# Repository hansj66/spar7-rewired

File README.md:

# Spar7 Rewired

This repository contains schematics, PCB layout, gerber files and STEP/STL files necessary for a complete Spar 7 rebuild.

 > **Disclaimer:** This repository contains information about my own rebuild. I can not guarantee that this will work as expected in YOUR game. It is entirely possible that you will break your beautiful collector quality game beyond repair trying to retrofit this board and the 3D printed hopper mechanism. Proceed at your own risk :)

Note: The payout slide is currently made of 1.7mm thick 3D printed plastic. This part will wear out over time, and the life expectancy of this part is currently unknown. A CNC fabricated aluminium/steel sheet with 3D printed endcaps is a better option if this is a concern.

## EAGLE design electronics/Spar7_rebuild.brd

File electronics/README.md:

# Eagle files

Here you will find a bill of materials along with eagle project files. Gerber files that can be uploaded to a PCB manufacturer can be found in the CAM folder

## Notes
1. There is no hardware debouncing in this version. A RC filter + schmitt trigger should be added to the inputs if you are planing on using interrupt handlers for the inputs.
2. The relay is rated for higher voltages than 12V, but I would not recommend using this for controlling a line voltage driven AC motor (220V can kill).
3. The 3.3V, 12V and USB leds are a bit on the bright side. Use series resistors with a higher resistance or consider not mounting these LEDs if light leakage to the payout slot is considered annoying.

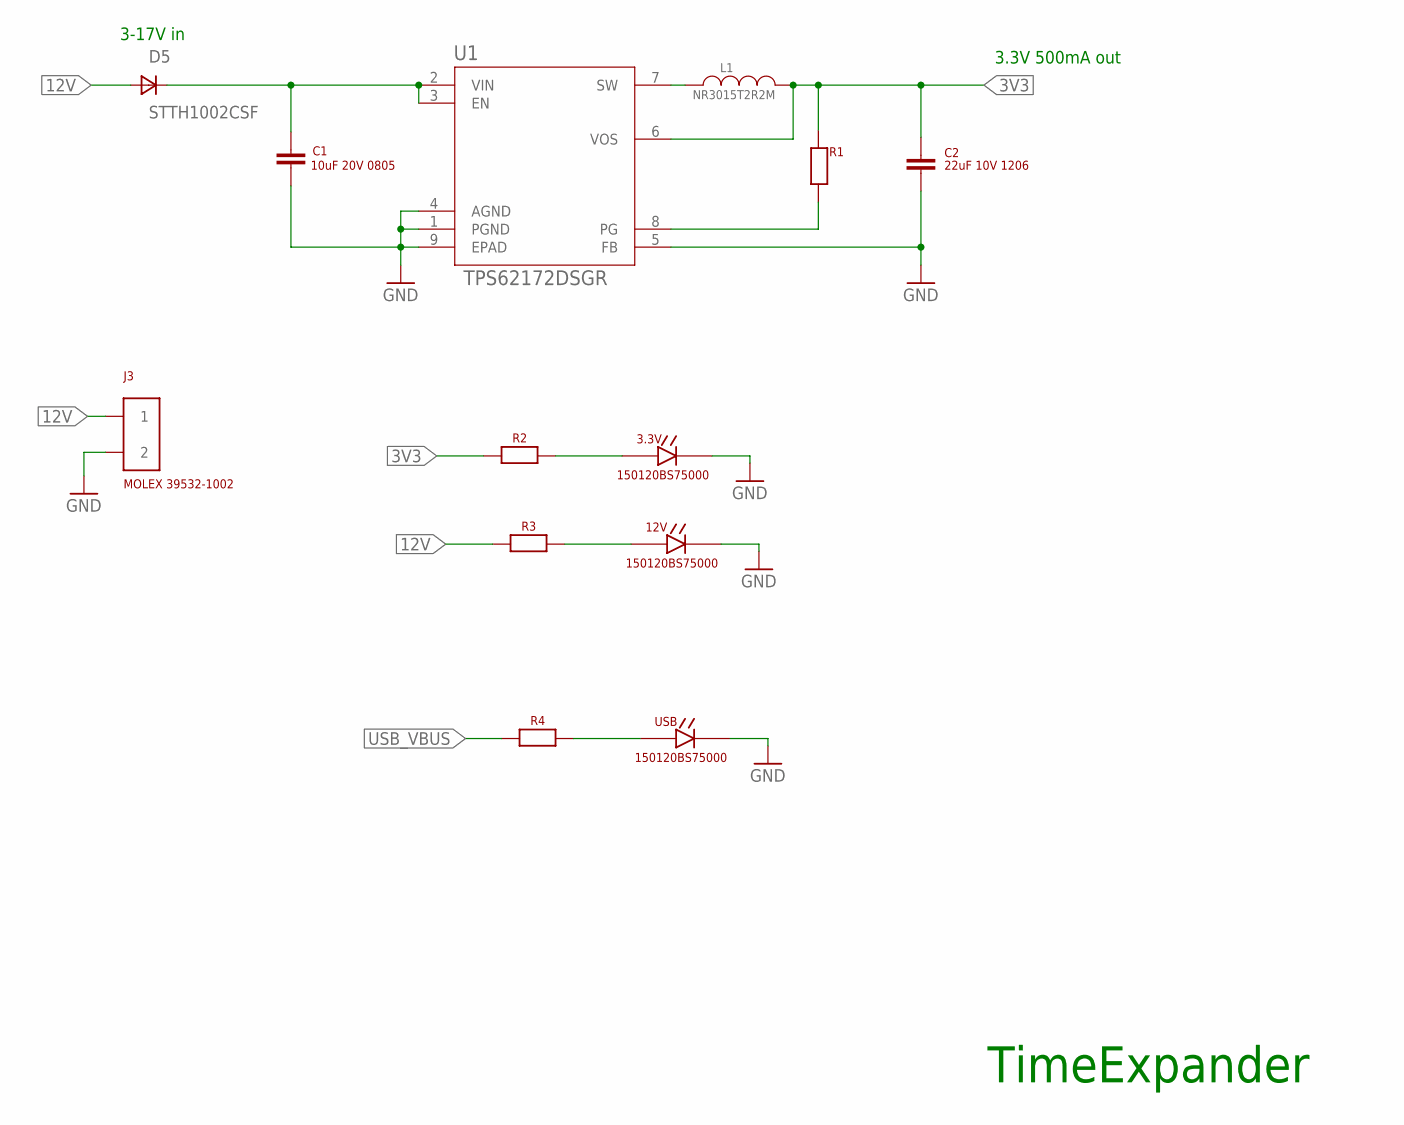
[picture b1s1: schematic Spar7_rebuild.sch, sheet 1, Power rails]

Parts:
3.3V, 12V: 150120BS75000
C1: 10uF 20V 0805; CAP_0805
C2: 22uF 10V 1206; CAP_1206
D5: STTH1002CSF; DIODE_STTH1002CSF
J3: MOLEX-39532-1002
L1: NR3015T2R2M; IND_TAIYO_NR3015_TAY
R1, R2, R3, R4: RESISTOR0402; RES_0402
U1: TPS62172DSGR; DSG8_1P6X0P9
USB: 150120BS75000

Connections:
3V3: C2.P$1 (1), L1.1, R1.P$1, R2.P$1, U1.6 (VOS); also elsewhere on the board
12V: D5.A1 (A), D5.A2 (A), J3.1, R3.P$1; also elsewhere on the board
GND: 3.3V.C, 12V.C, C1.P$2 (2), C2.P$2 (2), J3.2, U1.1 (PGND), U1.4 (AGND), U1.5 (FB), U1.9 (EPAD), USB.C; also elsewhere on the board
unnamed: L1.2, U1.7 (SW)
unnamed: 12V.A, R3.P$2
unnamed: R1.P$2, U1.8 (PG)
unnamed: R4.P$2, USB.A
unnamed: 3.3V.A, R2.P$2
unnamed: C1.P$1 (1), D5.C, U1.2 (VIN), U1.3 (EN)
USB_VBUS: R4.P$1; also elsewhere on the board

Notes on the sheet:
3.3V 500mA out
3-17V in
TimeExpander

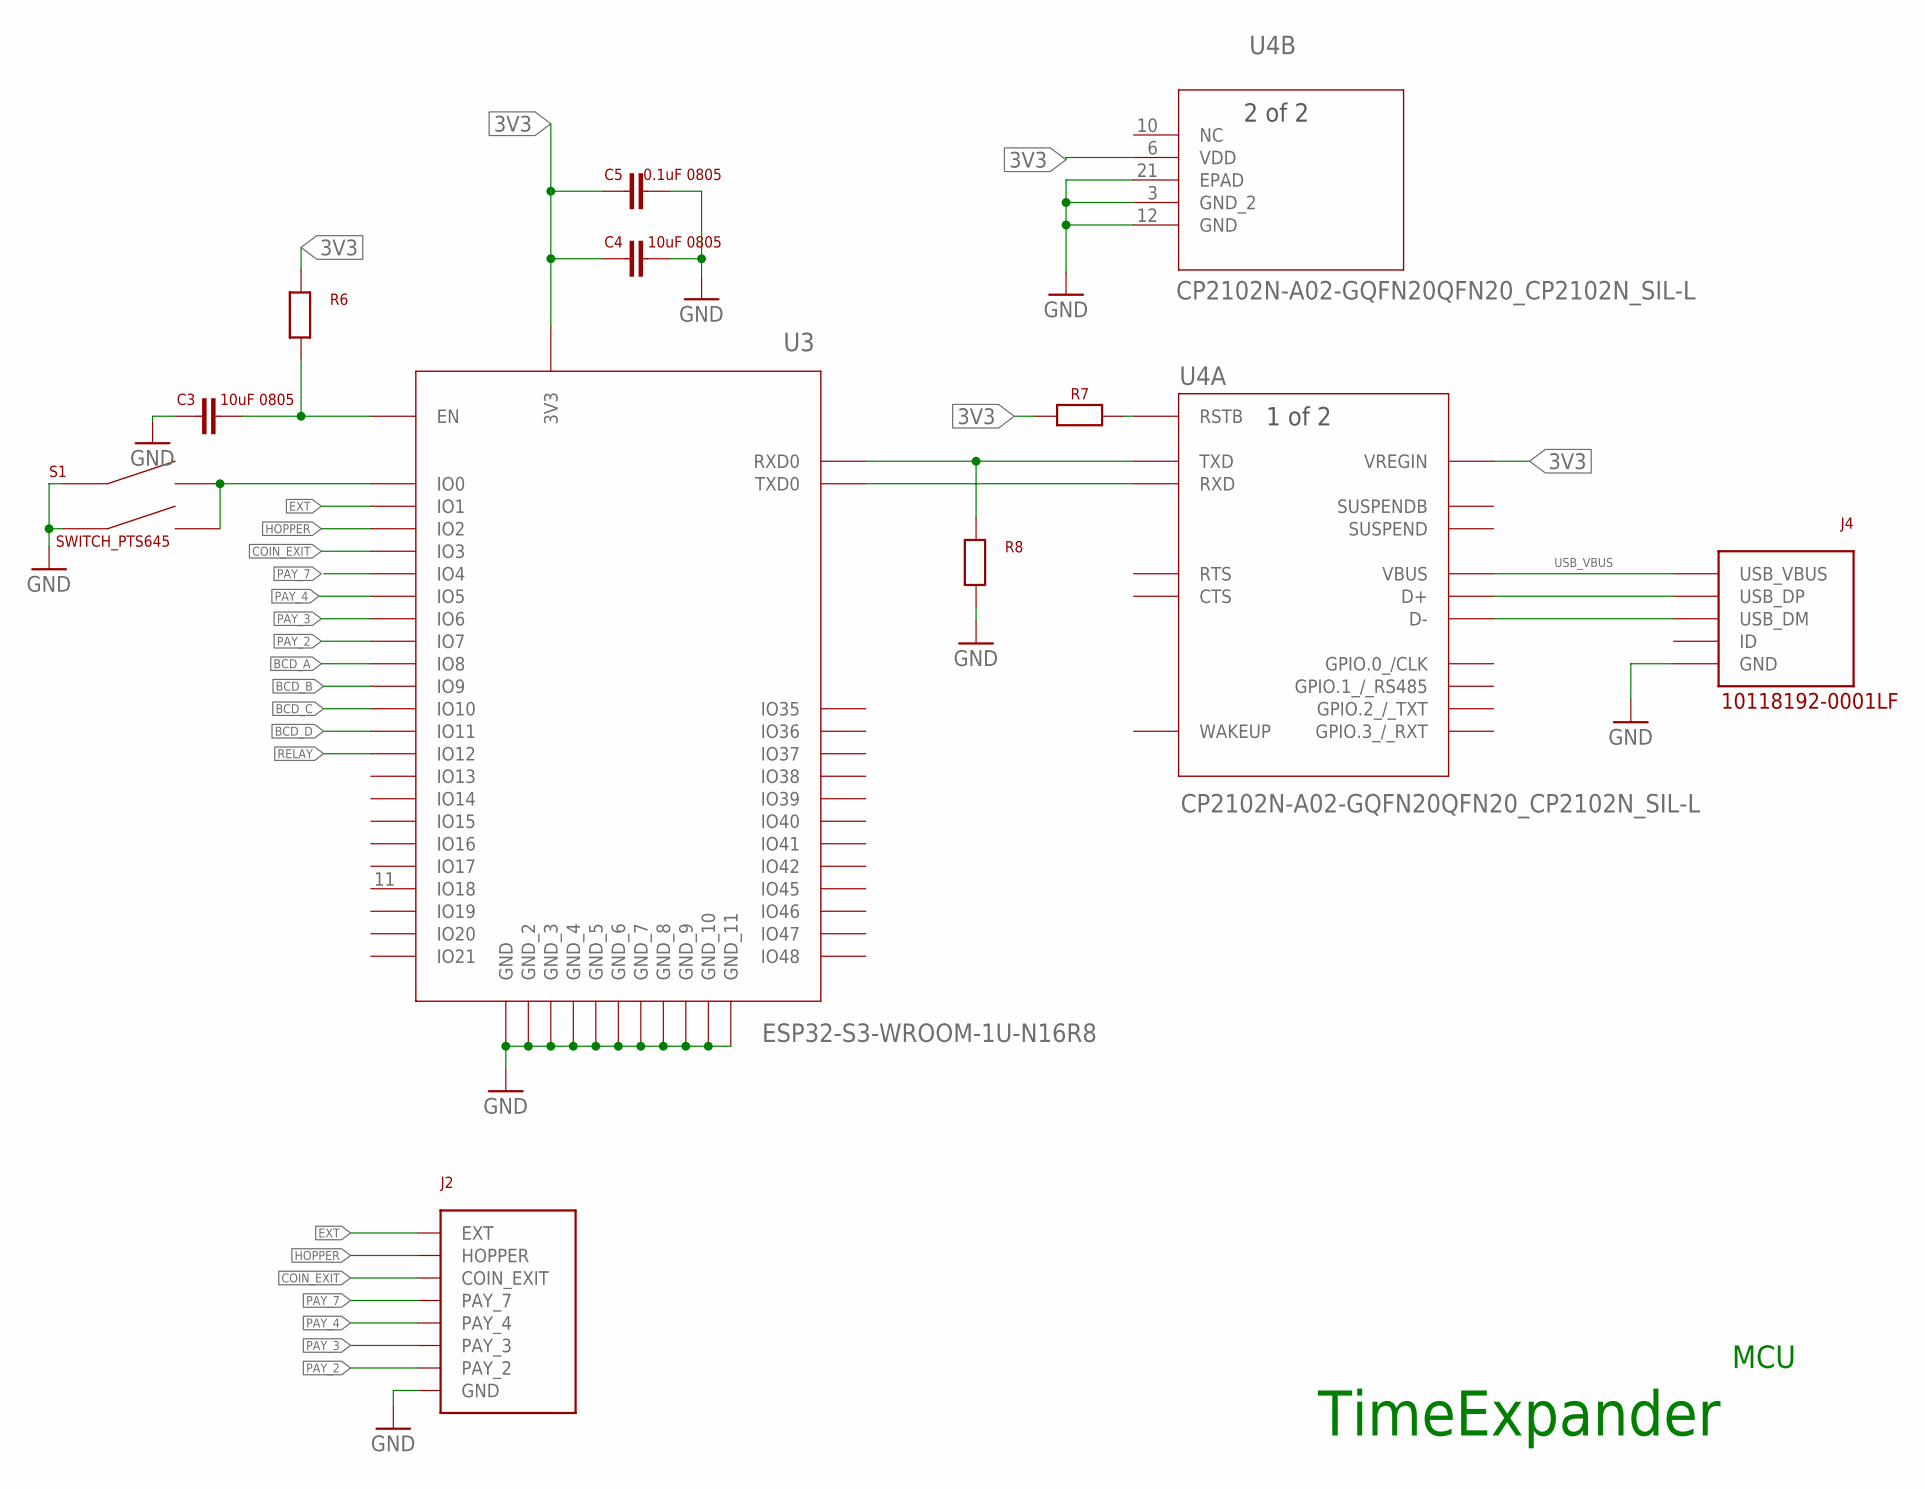
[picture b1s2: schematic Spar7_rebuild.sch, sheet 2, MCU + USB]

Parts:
C3, C4: 10uF 0805; CAP_0805
C5: 0.1uF 0805; CAP_0805
J2: SPAR7_REWIRED_TERM_BLOCK
J4: 10118192-0001LF; USB_RCPT_10118192-0001LF
R6, R7, R8: RESISTOR0402; RES_0402
S1: SWITCH_PTS645; SWITCH_PTS645_EE_NBIOT_01
U3: ESP32-S3-WROOM-1U-N16R8; ESP32­S3­WROOM­1U_EXP
U4: CP2102N-A02-GQFN20QFN20_CP2102N_SIL-L; QFN20_CP2102N_SIL-L

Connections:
3V3: C4.P$1 (1), C5.P$1 (1), R6.P$2, R7.P$1, U3.2 (3V3), U4.6 (VDD), U4.7 (VREGIN); also elsewhere on the board
BCD_A: U3.12 (IO8); also elsewhere on the board
BCD_B: U3.17 (IO9); also elsewhere on the board
BCD_C: U3.18 (IO10); also elsewhere on the board
BCD_D: U3.19 (IO11); also elsewhere on the board
COIN_EXIT: J2.COIN_EXIT, U3.15 (IO3)
EXT: J2.EXT, U3.39 (IO1)
GND: C3.P$1 (1), C4.P$2 (2), C5.P$2 (2), J2.GND, J4.GND, R8.P$1, S1.A1, S1.A2, U3.1 (GND_2), U3.40 (GND_3), U3.41 (GND_4), U3.42 (GND_5), U3.43 (GND_6), U3.44 (GND_7), U3.45 (GND_8), U3.46 (GND_9), U3.47 (GND_10), U3.48 (GND_11), U3.49 (GND), U4.3 (GND_2), U4.12 (GND), U4.21 (EPAD); also elsewhere on the board
HOPPER: J2.HOPPER, U3.38 (IO2)
unnamed: J4.D+ (USB_DP), U4.4 (D+)
unnamed: J4.D- (USB_DM), U4.5 (D-)
unnamed: R7.P$2, U4.9 (RSTB)
unnamed: R8.P$2, U3.36 (RXD0), U4.18 (TXD)
unnamed: U3.37 (TXD0), U4.17 (RXD)
unnamed: S1.B1, S1.B2, U3.27 (IO0)
unnamed: C3.P$2 (2), R6.P$1, U3.3 (EN)
PAY_2: J2.PAY_2, U3.7 (IO7)
PAY_3: J2.PAY_3, U3.6 (IO6)
PAY_4: J2.PAY_4, U3.5 (IO5)
PAY_7: J2.PAY_7, U3.4 (IO4)
RELAY: U3.20 (IO12); also elsewhere on the board
USB_VBUS: J4.VCC (USB_VBUS), U4.8 (VBUS); also elsewhere on the board

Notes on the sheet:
TimeExpander
MCU

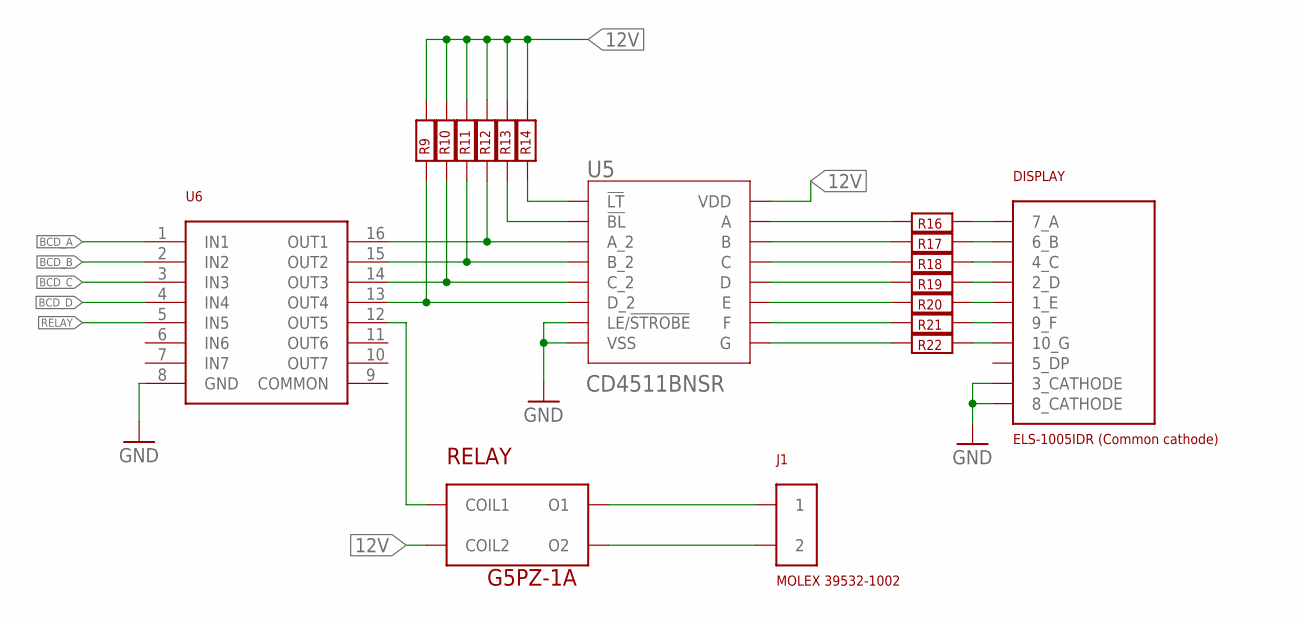
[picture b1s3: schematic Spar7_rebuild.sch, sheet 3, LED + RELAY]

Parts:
DISPLAY: ELS-1005IDR-SA10-21EWA
J1: MOLEX-39532-1002
R9, R10, R11, R12, R13, R14, R16, R17, R18, R19, R20, R21, R22: RESISTOR0402; RES_0402
RELAY: G5PZ-1A_RELAY
U5: CD4511BNSR; NS16
U6: ULN2003D1013TR; SO16-NARROW

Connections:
12V: R9.P$2, R10.P$2, R11.P$2, R12.P$2, R13.P$2, R14.P$2, RELAY.COIL2, U5.16 (VDD); also elsewhere on the board
BCD_A: U6.1 (IN1); also elsewhere on the board
BCD_B: U6.2 (IN2); also elsewhere on the board
BCD_C: U6.3 (IN3); also elsewhere on the board
BCD_D: U6.4 (IN4); also elsewhere on the board
GND: DISPLAY.3_CATHODE, DISPLAY.8_CATHODE, U5.5 (LE/!STROBE), U5.8 (VSS), U6.8 (GND); also elsewhere on the board
unnamed: J1.1, RELAY.O1
unnamed: DISPLAY.7_A, R16.P$1
unnamed: DISPLAY.6_B, R17.P$1
unnamed: DISPLAY.4_C, R18.P$1
unnamed: DISPLAY.2_D, R19.P$1
unnamed: DISPLAY.1_E, R20.P$1
unnamed: DISPLAY.9_F, R21.P$1
unnamed: DISPLAY.10_G, R22.P$1
unnamed: R16.P$2, U5.13 (A)
unnamed: R17.P$2, U5.12 (B)
unnamed: R18.P$2, U5.11 (C)
unnamed: R19.P$2, U5.10 (D)
unnamed: R20.P$2, U5.9 (E)
unnamed: R21.P$2, U5.15 (F)
unnamed: R22.P$2, U5.14 (G)
unnamed: R14.P$1, U5.3 (!LT)
unnamed: R13.P$1, U5.4 (!BL)
unnamed: R12.P$1, U5.7 (A_2), U6.16 (OUT1)
unnamed: R11.P$1, U5.1 (B_2), U6.15 (OUT2)
unnamed: R10.P$1, U5.2 (C_2), U6.14 (OUT3)
unnamed: R9.P$1, U5.6 (D_2), U6.13 (OUT4)
unnamed: RELAY.COIL1, U6.12 (OUT5)
unnamed: J1.2, RELAY.O2
RELAY: U6.5 (IN5); also elsewhere on the board

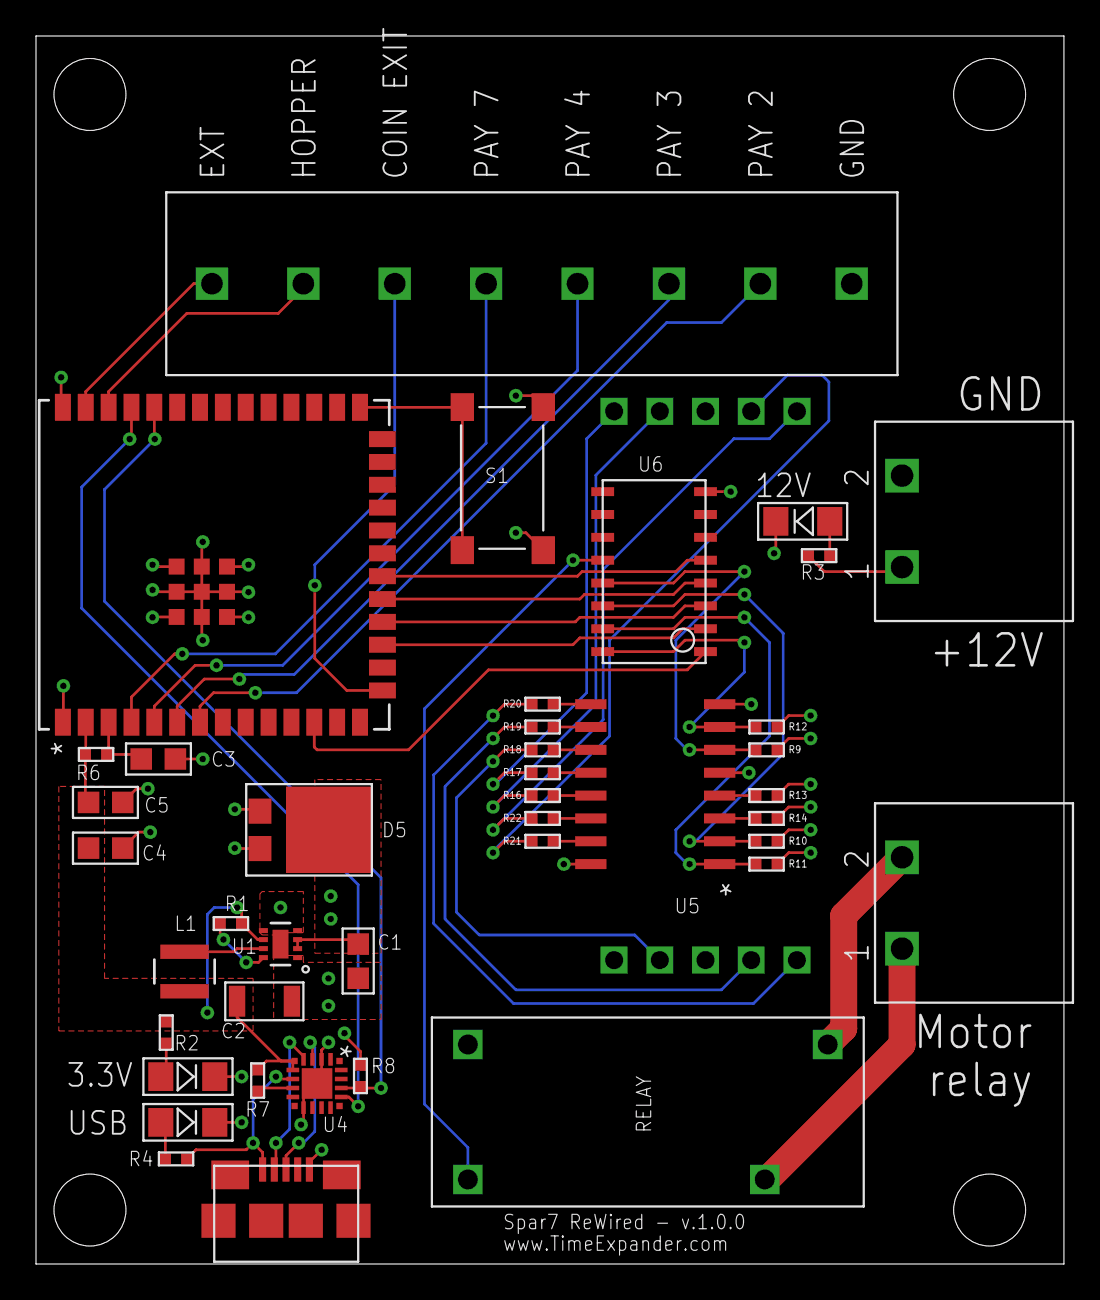
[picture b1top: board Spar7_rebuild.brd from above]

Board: 4 copper layers, 57.1 x 68.2 mm, 42 parts (1 on the bottom side), 52 nets.

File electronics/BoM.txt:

Partlist 

Part    Value                                 Device                                Package                   Description 

C1      10uF 20V 0805                         CAPACITOR0805                         CAP_0805                              
C2      22uF 10V 1206                         CAPACITOR1206                         CAP_1206                              
C3      10uF 0805                             CAPACITOR0805                         CAP_0805                              
C4      10uF 0805                             CAPACITOR0805                         CAP_0805                              
C5      0.1uF 0805                            CAPACITOR0805                         CAP_0805                              

D5      STTH1002CSF                           DIODESTTH1002CSF                      DIODE_STTH1002CSF                     

L1      NR3015T2R2M                           NR3015T2R2M                           IND_TAIYO_NR3015_TAY                  
R1      100k                                  RESISTOR0402                          RES_0402                              
R2      Beregn fra 3.3                        RESISTOR0402                          RES_0402                              
R3      Beregn fra 12                         RESISTOR0402                          RES_0402                              
R4      Beregn fra 5                          RESISTOR0402                          RES_0402                              
R6      10k 0402                              RESISTOR0402                          RES_0402                              
R7      10k 0402                              RESISTOR0402                          RES_0402                              
R8      10k 0402                              RESISTOR0402                          RES_0402                              
R9      10k 0402                              RESISTOR0402                          RES_0402                              
R10     10k 0402                              RESISTOR0402                          RES_0402                              
R11     10k 0402                              RESISTOR0402                          RES_0402                              
R12     10k 0402                              RESISTOR0402                          RES_0402                              
R13     10k 0402                              RESISTOR0402                          RES_0402                              
R14     10k 0402                              RESISTOR0402                          RES_0402                              
R16     510ohm 1/4W 402                       RESISTOR0402                          RES_0402                              
R17     510ohm 1/4W 402                       RESISTOR0402                          RES_0402                              
R18     510ohm 1/4W 402                       RESISTOR0402                          RES_0402                              
R19     510ohm 1/4W 402                       RESISTOR0402                          RES_0402                              
R20     510ohm 1/4W 402                       RESISTOR0402                          RES_0402                              
R21     510ohm 1/4W 402                       RESISTOR0402                          RES_0402                              
R22     510ohm 1/4W 402                       RESISTOR0402                          RES_0402                              

RELAY   G5PZ-1A_RELAY                         G5PZ-1A_RELAY                         G5PZ-1A_RELAY                         
S1      SWITCH_PTS645                         SWITCH_PTS645                         SWITCH_PTS645_EE_NBIOT_01             

U1      TPS62172DSGR                          TPS62173DSGR                          DSG8_1P6X0P9                          
U3      ESP32-S3-WROOM-1U-N16R8               ESP32-S3-WROOM-1U-N16R8               ESP32­S3­WROOM­1U_EXP                 
U4      CP2102N-A02-GQFN20QFN20_CP2102N_SIL-L CP2102N-A02-GQFN20QFN20_CP2102N_SIL-L QFN20_CP2102N_SIL-L                   
U5      CD4511BNSR                            CD4511BNSR                            NS16                                  
U6      ULN2003D1013TR                        ULN2003D1013TR                        SO16-NARROW                           

3.3V    150120BS75000                         LED150120BS75000                      150120BS75000                         
12V     150120BS75000                         LED150120BS75000                      150120BS75000                         
USB     150120BS75000                         LED150120BS75000                      150120BS75000                         


J1      MOLEX-39532-1002                      MOLEX-39532-1002                      MOLEX-39532-1002                      
J2      SPAR7_REWIRED_TERM_BLOCK              SPAR7_REWIRED_TERM_BLOCK              SPAR7_REWIRED_TERM_BLOCK              
J3      MOLEX-39532-1002                      MOLEX-39532-1002                      MOLEX-39532-1002                      
J4      10118192-0001LF                       USB_RCPT_10118192-0001LF              USB_RCPT_10118192-0001LF              

DISPLAY 7 segment common cathode display (ELS-1005IDR or equivalent)               

Hopper switch: SS-5GL2-FT

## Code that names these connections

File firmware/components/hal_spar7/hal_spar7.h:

#ifndef _HAL_SPAR7_H_
#define _HAL_SPAR7_H_

// Output
//
#define GPIO_BCD_BASE 8
#define GPIO_BCD_A 8
#define GPIO_BCD_B 9
#define GPIO_BCD_C 10
#define GPIO_BCD_D 11
#define GPIO_RELAY 12

#define GPIO_OUTPUT_PIN_SEL  ((1ULL<<GPIO_BCD_BASE) | (1ULL<<GPIO_BCD_A) | (1ULL<<GPIO_BCD_B) | (1ULL<<GPIO_BCD_C) | (1ULL<<GPIO_BCD_D) | (1ULL<<GPIO_RELAY))

// Input
//
#define GPIO_EXT 1
#define GPIO_HOPPER 2
#define GPIO_COIN_EXIT 3
#define GPIO_PAY7 4
#define GPIO_PAY4 5
#define GPIO_PAY3 6
#define GPIO_PAY2 7

#define GPIO_INPUT_PIN_SEL  ((1ULL<<GPIO_EXT) | (1ULL<<GPIO_HOPPER) | (1ULL<<GPIO_COIN_EXIT) | (1ULL<<GPIO_PAY7) | (1ULL<<GPIO_PAY4) | (1ULL<<GPIO_PAY3) | (1ULL<<GPIO_PAY2))

void display_digit(int digit);
void start_motor();
void stop_motor();
void init_gpio();


#endif

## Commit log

2024-01-04 added brd + sch
2024-01-04 added BoM
2024-01-05 Added skeleton firmware
2024-01-08 Added Spiffs partition
    * Added script for generating spiffs image from certs\chain
    * Added automatic flashing of spiffs image
2024-01-09 Added networking
    * coap
    * wifi
    * dtls
2024-01-13 Game logic is starting to show signs of life
2024-01-31 Create LICENSE
2024-02-01 Added shell
    * cmd for get/set debounce
    * cmd for get/set wifi credentials
2024-02-02 DTLS ok
2024-02-03 Fixed wifi
    * fixed display bug
2024-02-03 Added pics
2024-02-03 Updated README
    * Added more pictures
2024-02-03 Removed redundant config
2024-02-03 Removed spiffs binary
2024-02-03 Removed todo.txt

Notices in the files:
parts and their libraries:
TimeExpander2: COPYRIGHT: Copyright (C) 2023 Ultra Librarian. All rights reserved.
